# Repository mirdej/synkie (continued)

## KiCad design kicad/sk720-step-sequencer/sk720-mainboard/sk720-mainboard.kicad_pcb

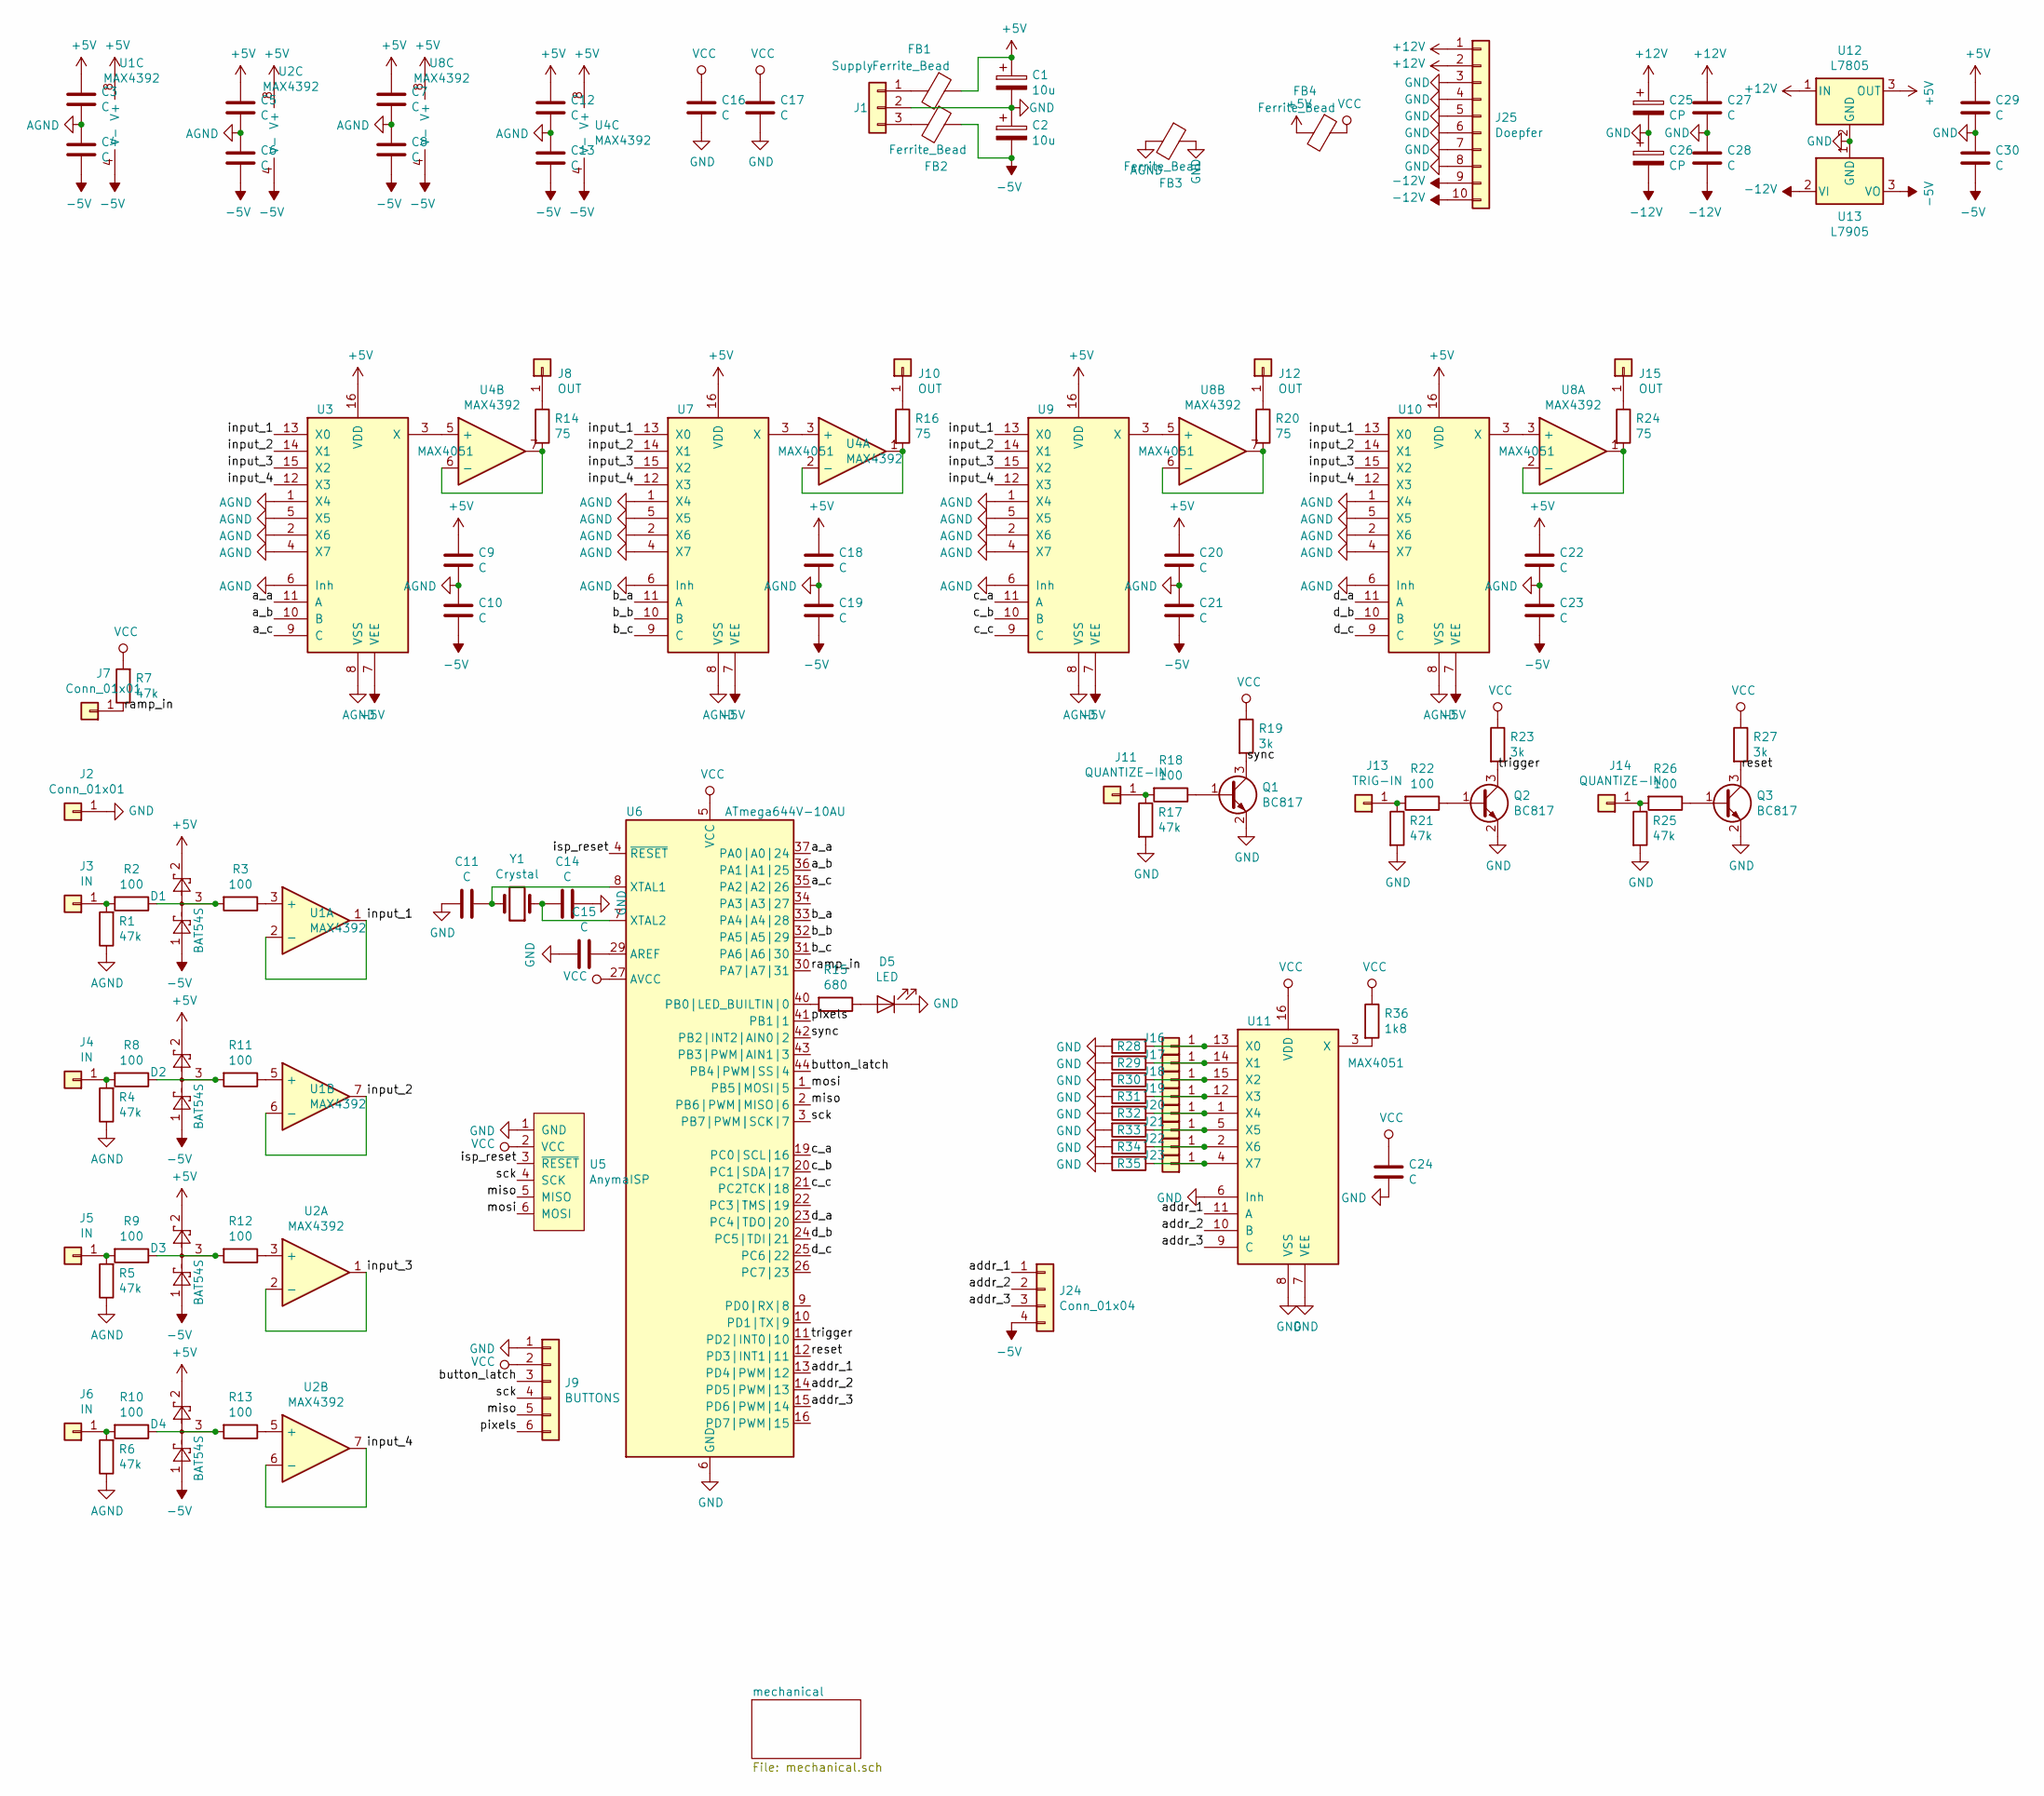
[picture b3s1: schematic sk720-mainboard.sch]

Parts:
C1, C2: 10u; CP_EIA-3528-21_Kemet-B
C3, C4, C5, C6, C7, C8, C9, C10, C11, C12, C13, C14, C15, C16, C17, C18, C19, C20, C21, C22, C23, C24, C27, C28, C29, C30: C; C_0603_1608Metric_Pad1.05x0.95mm_HandSolder
C25, C26: CP; CP_EIA-3528-21_Kemet-B_Pad1.50x2.35mm_HandSolder
D1, D2, D3, D4: BAT54S; SOT-23
D5: LED; LED_D3.0mm
FB1, FB2, FB3, FB4: Ferrite_Bead; L_1206_3216Metric_Pad1.42x1.75mm_HandSolder
J1: Supply; Molex_KK-254_AE-6410-03A_1x03_P2.54mm_Vertical
J2, J7: Conn_01x01; Solderpad_1mm
J3, J4, J5, J6: IN; Solderpad_1mm
J8, J10, J12, J15: OUT; Solderpad_1mm
J9: BUTTONS; PinHeader_1x06_P2.54mm_Vertical
J11, J14: QUANTIZE-IN; Solderpad_1mm
J13: TRIG-IN; Solderpad_1mm
J16, J17, J18, J19, J20, J21, J22, J23: TRIG; Solderpad_1mm
J24: Conn_01x04; PinHeader_1x04_P2.54mm_Vertical
J25: Doepfer; PinHeader_2x05_P2.54mm_Vertical
Q1, Q2, Q3: BC817; SOT-23
R1, R4, R5, R6, R7, R17, R21, R25: 47k; R_0805_2012Metric_Pad1.15x1.40mm_HandSolder
R2, R3, R8, R9, R10, R11, R12, R13, R18, R22, R26: 100; R_0805_2012Metric_Pad1.15x1.40mm_HandSolder
R14, R16, R20, R24: 75; R_0805_2012Metric_Pad1.15x1.40mm_HandSolder
R15: 680; R_0805_2012Metric_Pad1.15x1.40mm_HandSolder
R19, R23, R27: 3k; R_0805_2012Metric_Pad1.15x1.40mm_HandSolder
R28, R29, R30, R31, R32, R33, R34, R35: 300; R_0805_2012Metric_Pad1.15x1.40mm_HandSolder
R36: 1k8; R_0805_2012Metric_Pad1.15x1.40mm_HandSolder
U1, U2, U4, U8: MAX4392; SOIC-8_3.9x4.9mm_P1.27mm
U3, U7, U9, U10, U11: MAX4051; SOIC-16_3.9x9.9mm_P1.27mm
U5: AnymaISP; PinHeader_1x06_P2.54mm_Vertical
U6: ATmega644V-10AU; TQFP-44_10x10mm_P0.8mm
U12: L7805; TO-220-3_Horizontal_TabDown
U13: L7905; TO-220-3_Horizontal_TabDown
Y1: Crystal; Crystal_SMD_HC49-SD

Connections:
+5V: C1.1, C3.1, C5.1, C7.1, C9.1, C12.1, C18.1, C20.1, C22.1, C29.1, D1.2, D2.2, D3.2, D4.2, FB1.1, FB4.2, U1.8 (V+), U2.8 (V+), U3.16 (VDD), U4.8 (V+), U7.16 (VDD), U8.8 (V+), U9.16 (VDD), U10.16 (VDD), U12.3 (OUT)
+12V: C25.1, C27.1, J25.1, J25.2, U12.1 (IN)
-5V: C2.2, C4.2, C6.2, C8.2, C10.2, C13.2, C19.2, C21.2, C23.2, C30.2, D1.1, D2.1, D3.1, D4.1, FB2.1, J24.4, U1.4 (V-), U2.4 (V-), U3.7 (VEE), U4.4 (V-), U7.7 (VEE), U8.4 (V-), U9.7 (VEE), U10.7 (VEE), U13.3 (VO)
-12V: C26.2, C28.2, J25.9, J25.10, U13.2 (VI)
/a_a: U3.11 (A), U6.37 (PA0|A0|24)
/a_b: U3.10 (B), U6.36 (PA1|A1|25)
/a_c: U3.9 (C), U6.35 (PA2|A2|26)
/addr_1: J24.1, U6.13 (PD4|PWM|12), U11.11 (A)
/addr_2: J24.2, U6.14 (PD5|PWM|13), U11.10 (B)
/addr_3: J24.3, U6.15 (PD6|PWM|14), U11.9 (C)
/b_a: U6.33 (PA4|A4|28), U7.11 (A)
/b_b: U6.32 (PA5|A5|29), U7.10 (B)
/b_c: U6.31 (PA6|A6|30), U7.9 (C)
/button_latch: J9.3, U6.44 (PB4|PWM|SS|4)
/c_a: U6.19 (PC0|SCL|16), U9.11 (A)
/c_b: U6.20 (PC1|SDA|17), U9.10 (B)
/c_c: U6.21 (PC2TCK|18), U9.9 (C)
/d_a: U6.23 (PC4|TDO|20), U10.11 (A)
/d_b: U6.24 (PC5|TDI|21), U10.10 (B)
/d_c: U6.25 (PC6|22), U10.9 (C)
/input_1: U1.1, U1.2 (-), U3.13 (X0), U7.13 (X0), U9.13 (X0), U10.13 (X0)
/input_2: U1.6 (-), U1.7, U3.14 (X1), U7.14 (X1), U9.14 (X1), U10.14 (X1)
/input_3: U2.1, U2.2 (-), U3.15 (X2), U7.15 (X2), U9.15 (X2), U10.15 (X2)
/input_4: U2.6 (-), U2.7, U3.12 (X3), U7.12 (X3), U9.12 (X3), U10.12 (X3)
/isp_reset: U5.3 (~RESET), U6.4 (~RESET)
/miso: J9.5, U5.5 (MISO), U6.2 (PB6|PWM|MISO|6)
/mosi: U5.6 (MOSI), U6.1 (PB5|MOSI|5)
/pixels: J9.6, U6.41 (PB1|1)
/ramp_in: J7.1, R7.1, U6.30 (PA7|A7|31)
/reset: Q3.3 (C), R27.2, U6.12 (PD3|INT1|11)
/sck: J9.4, U5.4 (SCK), U6.3 (PB7|PWM|SCK|7)
/sync: Q1.3 (C), R19.2, U6.42 (PB2|INT2|AIN0|2)
/trigger: Q2.3 (C), R23.2, U6.11 (PD2|INT0|10)
AGND: C3.2, C4.1, C5.2, C6.1, C7.2, C8.1, C9.2, C10.1, C12.2, C13.1, C18.2, C19.1, C20.2, C21.1, C22.2, C23.1, FB3.2, R1.1, R4.1, R5.1, R6.1, U3.1 (X4), U3.2 (X6), U3.4 (X7), U3.5 (X5), U3.6 (Inh), U3.8 (VSS), U7.1 (X4), U7.2 (X6), U7.4 (X7), U7.5 (X5), U7.6 (Inh), U7.8 (VSS), U9.1 (X4), U9.2 (X6), U9.4 (X7), U9.5 (X5), U9.6 (Inh), U9.8 (VSS), U10.1 (X4), U10.2 (X6), U10.4 (X7), U10.5 (X5), U10.6 (Inh), U10.8 (VSS)
GND: C1.2, C2.1, C11.2, C14.1, C15.2, C16.2, C17.2, C24.2, C25.2, C26.1, C27.2, C28.1, C29.2, C30.1, D5.1 (K), FB3.1, J1.2, J2.1, J9.1, J25.3, J25.4, J25.5, J25.6, J25.7, J25.8, Q1.2 (E), Q2.2 (E), Q3.2 (E), R17.2, R21.2, R25.2, R28.2, R29.2, R30.2, R31.2, R32.2, R33.2, R34.2, R35.2, U5.1 (GND), U6.6 (GND), U6.18 (GND), U6.28 (GND), U6.39 (GND), U11.6 (Inh), U11.7 (VEE), U11.8 (VSS), U12.2 (GND), U13.1 (GND); also elsewhere on the board
unnamed: C11.1, U6.8 (XTAL1), Y1.2
unnamed: C14.2, U6.7 (XTAL2), Y1.1
unnamed: C15.1, U6.29 (AREF)
unnamed: D1.3, R2.1, R3.2
unnamed: D2.3, R8.1, R11.2
unnamed: D3.3, R9.1, R12.2
unnamed: D4.3, R10.1, R13.2
unnamed: D5.2 (A), R15.1
unnamed: FB1.2, J1.1
unnamed: FB2.2, J1.3
unnamed: J3.1, R1.2, R2.2
unnamed: J4.1, R4.2, R8.2
unnamed: J5.1, R5.2, R9.2
unnamed: J6.1, R6.2, R10.2
unnamed: J8.1, R14.1
unnamed: J10.1, R16.1
unnamed: J11.1, R17.1, R18.2
unnamed: J12.1, R20.1
unnamed: J13.1, R21.1, R22.2
unnamed: J14.1, R25.1, R26.2
unnamed: J15.1, R24.1
unnamed: J16.1, R28.1, U11.13 (X0)
unnamed: J17.1, R29.1, U11.14 (X1)
unnamed: J18.1, R30.1, U11.15 (X2)
unnamed: J19.1, R31.1, U11.12 (X3)
unnamed: J20.1, R32.1, U11.1 (X4)
unnamed: J21.1, R33.1, U11.5 (X5)
unnamed: J22.1, R34.1, U11.2 (X6)
unnamed: J23.1, R35.1, U11.4 (X7)
unnamed: Q1.1 (B), R18.1
unnamed: Q2.1 (B), R22.1
unnamed: Q3.1 (B), R26.1
unnamed: R3.1, U1.3 (+)
unnamed: R11.1, U1.5 (+)
unnamed: R12.1, U2.3 (+)
unnamed: R13.1, U2.5 (+)
unnamed: R14.2, U4.6 (-), U4.7
unnamed: R15.2, U6.40 (PB0|LED_BUILTIN|0)
unnamed: R16.2, U4.1, U4.2 (-)
unnamed: R20.2, U8.6 (-), U8.7
unnamed: R24.2, U8.1, U8.2 (-)
unnamed: R36.2, U11.3 (X)
unnamed: U3.3 (X), U4.5 (+)
unnamed: U4.3 (+), U7.3 (X)
unnamed: U8.5 (+), U9.3 (X)
unnamed: U8.3 (+), U10.3 (X)
VCC: C16.1, C17.1, C24.1, FB4.1, J9.2, R7.2, R19.1, R23.1, R27.1, R36.1, U5.2 (VCC), U6.5 (VCC), U6.17 (VCC), U6.27 (AVCC), U6.38 (VCC), U11.16 (VDD)

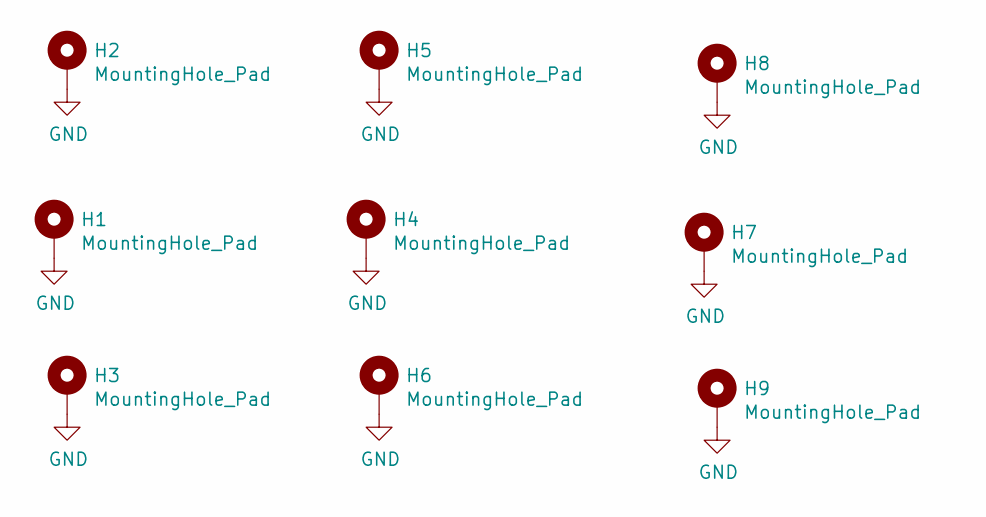
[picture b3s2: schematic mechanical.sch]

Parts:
H1, H2, H3, H4, H5, H6, H7, H8, H9: MountingHole_Pad; MountingHole_3.2mm_M3_ISO14580_Pad

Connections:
GND: H1.1, H2.1, H3.1, H4.1, H5.1, H6.1, H7.1, H8.1, H9.1; also elsewhere on the board

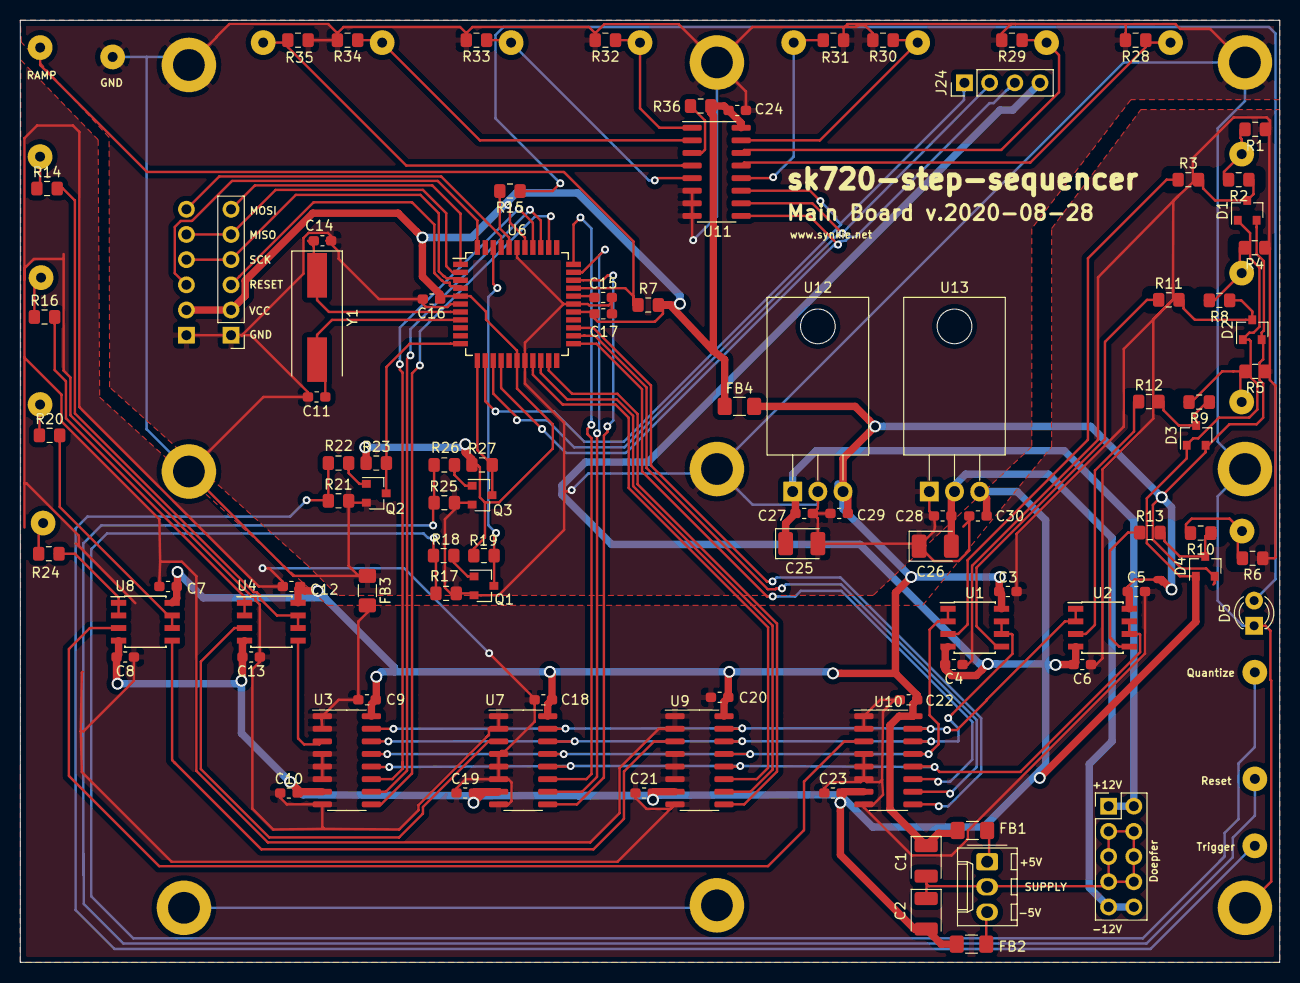
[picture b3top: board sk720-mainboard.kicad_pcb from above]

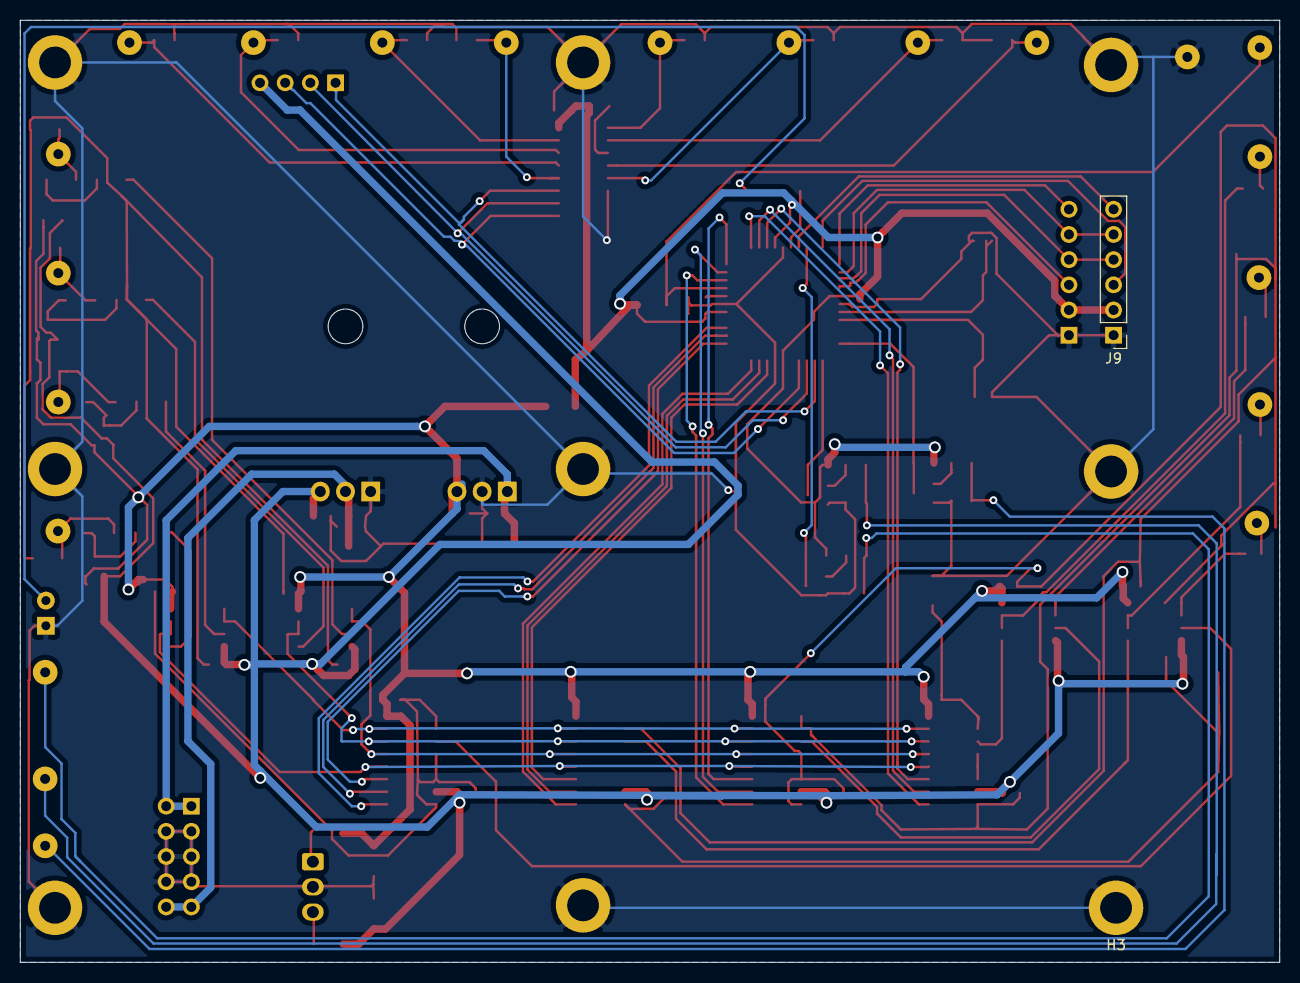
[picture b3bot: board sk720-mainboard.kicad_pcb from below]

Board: 2 copper layers, 127.0 x 95.0 mm, 126 parts (2 on the bottom side), 82 nets.

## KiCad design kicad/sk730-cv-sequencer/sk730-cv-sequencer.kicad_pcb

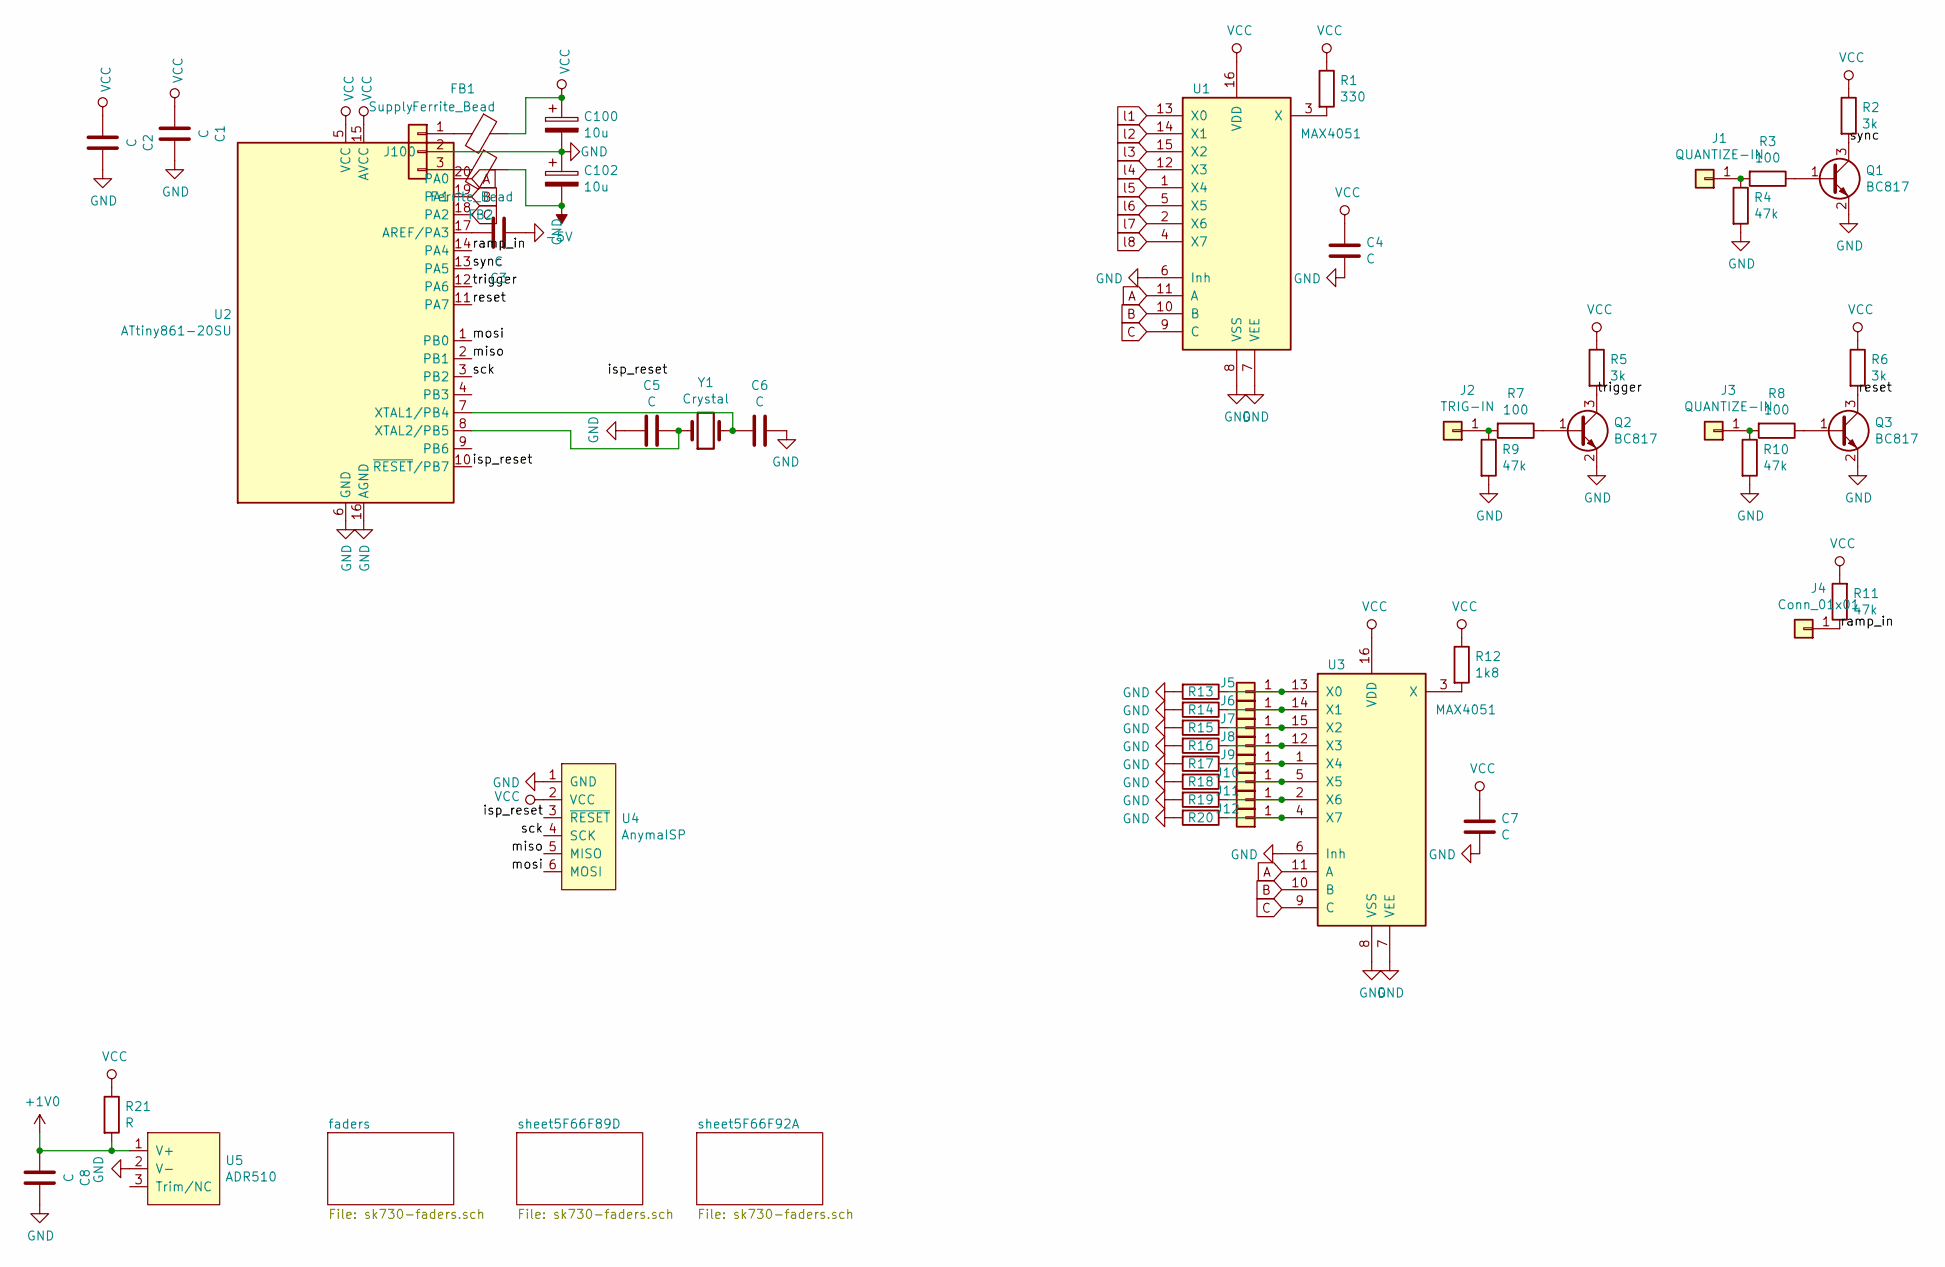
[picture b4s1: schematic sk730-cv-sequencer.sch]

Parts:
C1, C2, C3, C4, C7, C8: C; C_0603_1608Metric_Pad1.05x0.95mm_HandSolder
C5, C6: C; C_0805_2012Metric_Pad1.15x1.40mm_HandSolder
C100, C102: 10u; CP_EIA-3528-21_Kemet-B
FB1, FB2: Ferrite_Bead; L_1206_3216Metric_Pad1.42x1.75mm_HandSolder
J1, J3: QUANTIZE-IN; Solderpad_1mm
J2: TRIG-IN; Solderpad_1mm
J4: Conn_01x01; Solderpad_1mm
J5, J6, J7, J8, J9, J10, J11, J12: TRIG; Solderpad_1mm
J100: Supply; Molex_KK-254_AE-6410-03A_1x03_P2.54mm_Vertical
Q1, Q2, Q3: BC817; SOT-23
R1: 330; R_0805_2012Metric_Pad1.15x1.40mm_HandSolder
R2, R5, R6: 3k; R_0805_2012Metric_Pad1.15x1.40mm_HandSolder
R3, R7, R8: 100; R_0805_2012Metric_Pad1.15x1.40mm_HandSolder
R4, R9, R10, R11: 47k; R_0805_2012Metric_Pad1.15x1.40mm_HandSolder
R12: 1k8; R_0805_2012Metric_Pad1.15x1.40mm_HandSolder
R13, R14, R15, R16, R17, R18, R19, R20: 300; R_0805_2012Metric_Pad1.15x1.40mm_HandSolder
R21: R; C_0805_2012Metric_Pad1.15x1.40mm_HandSolder
U1, U3: MAX4051; SOIC-16_3.9x9.9mm_P1.27mm
U2: ATtiny861-20SU; SOIC-20W_7.5x12.8mm_P1.27mm
U4: AnymaISP; AnymaPOGO-ISP
U5: ADR510; SOT-23
Y1: Crystal; Crystal_SMD_HC49-SD

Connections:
+1V0: C8.2, R21.2, U5.1 (V+); also elsewhere on the board
-5V: C102.2, FB2.1; also elsewhere on the board
/isp_reset: U2.10 (~RESET~/PB7), U4.3 (~RESET)
/miso: U2.2 (PB1), U4.5 (MISO)
/mosi: U2.1 (PB0), U4.6 (MOSI)
/ramp_in: J4.1, R11.1, U2.14 (PA4)
/reset: Q3.3 (C), R6.2, U2.11 (PA7)
/sck: U2.3 (PB2), U4.4 (SCK)
/sync: Q1.3 (C), R2.2, U2.13 (PA5)
/trigger: Q2.3 (C), R5.2, U2.12 (PA6)
A: U1.11 (A), U2.20 (PA0), U3.11 (A); also elsewhere on the board
B: U1.10 (B), U2.19 (PA1), U3.10 (B); also elsewhere on the board
C: U1.9 (C), U2.18 (PA2), U3.9 (C); also elsewhere on the board
GND: C1.1, C2.1, C3.2, C4.2, C5.1, C6.2, C7.2, C8.1, C100.2, C102.1, J100.2, Q1.2 (E), Q2.2 (E), Q3.2 (E), R4.2, R9.2, R10.2, R13.2, R14.2, R15.2, R16.2, R17.2, R18.2, R19.2, R20.2, U1.6 (Inh), U1.7 (VEE), U1.8 (VSS), U2.6 (GND), U2.16 (AGND), U3.6 (Inh), U3.7 (VEE), U3.8 (VSS), U4.1 (GND), U5.2 (V-); also elsewhere on the board
unnamed: C3.1, U2.17 (AREF/PA3)
unnamed: C5.2, U2.8 (XTAL2/PB5), Y1.1
unnamed: C6.1, U2.7 (XTAL1/PB4), Y1.2
unnamed: FB1.2, J100.1
unnamed: FB2.2, J100.3
unnamed: J1.1, R3.2, R4.1
unnamed: J2.1, R7.2, R9.1
unnamed: J3.1, R8.2, R10.1
unnamed: J5.1, R13.1, U3.13 (X0)
unnamed: J6.1, R14.1, U3.14 (X1)
unnamed: J7.1, R15.1, U3.15 (X2)
unnamed: J8.1, R16.1, U3.12 (X3)
unnamed: J9.1, R17.1, U3.1 (X4)
unnamed: J10.1, R18.1, U3.5 (X5)
unnamed: J11.1, R19.1, U3.2 (X6)
unnamed: J12.1, R20.1, U3.4 (X7)
unnamed: Q1.1 (B), R3.1
unnamed: Q2.1 (B), R7.1
unnamed: Q3.1 (B), R8.1
unnamed: R1.2, U1.3 (X)
unnamed: R12.2, U3.3 (X)
VCC: C1.2, C2.2, C4.1, C7.1, C100.1, FB1.1, R1.1, R2.1, R5.1, R6.1, R11.2, R12.1, R21.1, U1.16 (VDD), U2.5 (VCC), U2.15 (AVCC), U3.16 (VDD), U4.2 (VCC); also elsewhere on the board
l1: U1.13 (X0); also elsewhere on the board
l2: U1.14 (X1); also elsewhere on the board
l3: U1.15 (X2); also elsewhere on the board
l4: U1.12 (X3); also elsewhere on the board
l5: U1.1 (X4); also elsewhere on the board
l6: U1.5 (X5); also elsewhere on the board
l7: U1.2 (X6); also elsewhere on the board
l8: U1.4 (X7); also elsewhere on the board

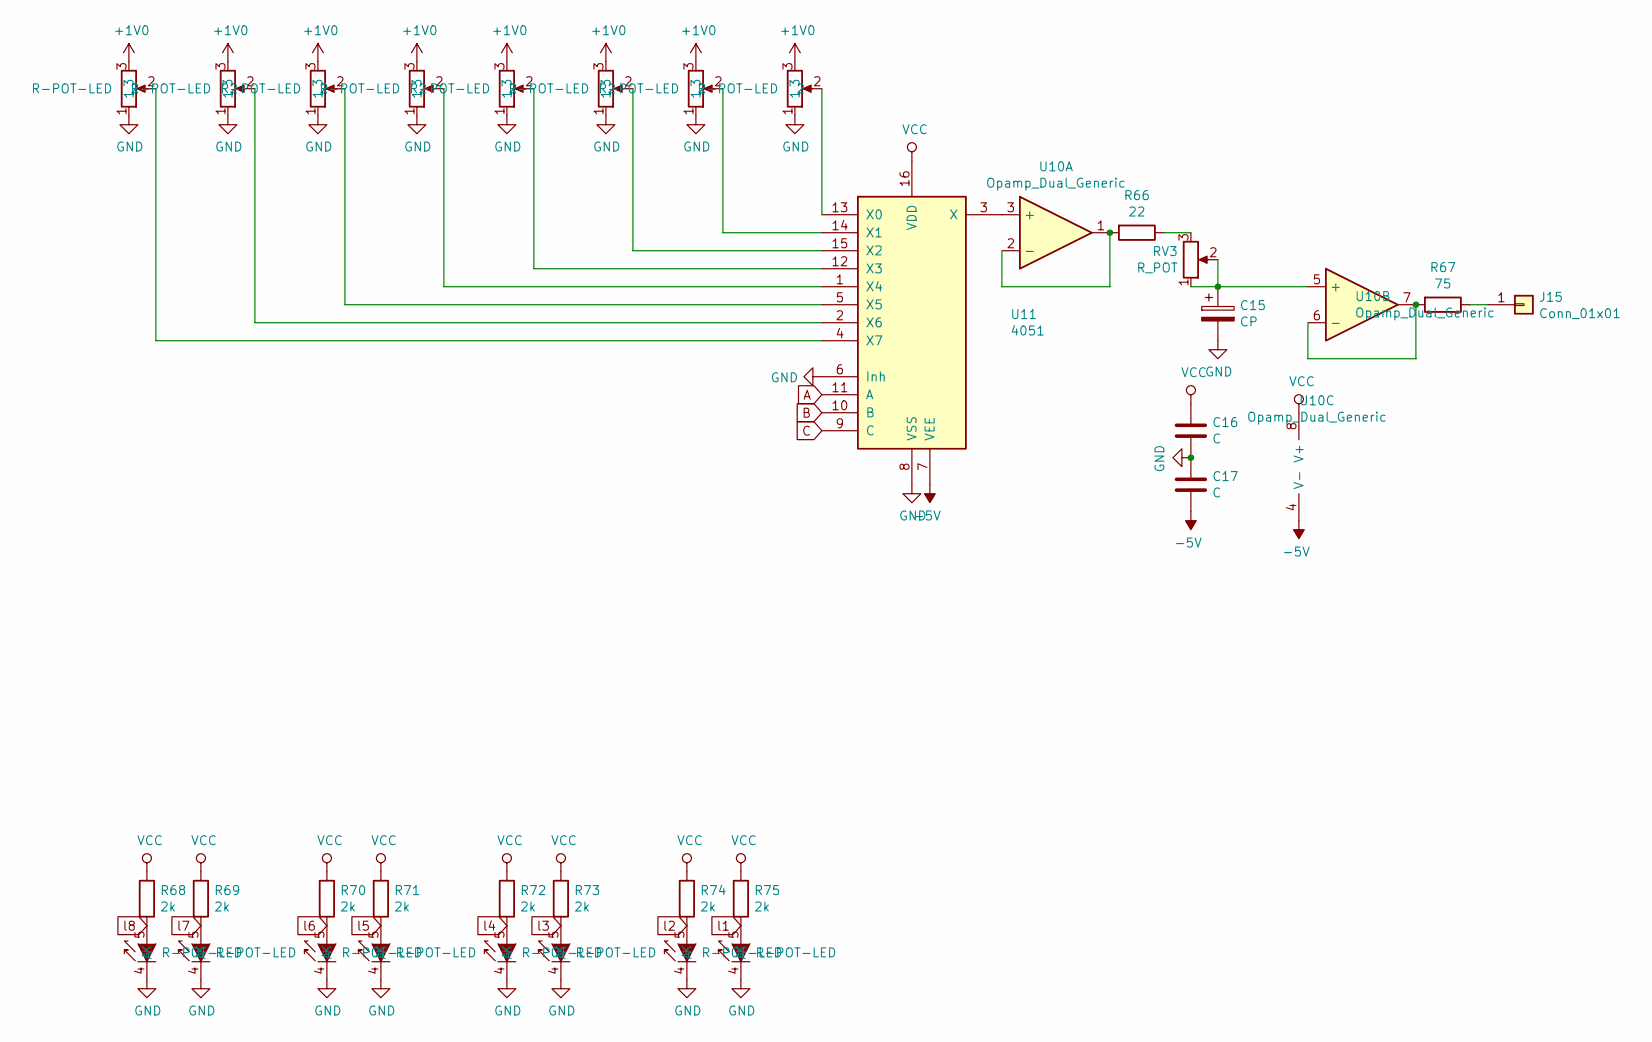
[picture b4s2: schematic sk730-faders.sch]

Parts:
C9: CP; CP_EIA-3528-21_Kemet-B_Pad1.50x2.35mm_HandSolder
C10, C11: C; C_0603_1608Metric_Pad1.05x0.95mm_HandSolder
J13: Conn_01x01; Solderpad_1mm
R22, R23, R24, R25, R26, R27, R28, R29: R-POT-LED; PTL20
R30: 22; C_0805_2012Metric_Pad1.15x1.40mm_HandSolder
R31: 75; C_0805_2012Metric_Pad1.15x1.40mm_HandSolder
R32, R33, R34, R35, R36, R37, R38, R39: 2k; R_0805_2012Metric_Pad1.15x1.40mm_HandSolder
RV1: R_POT; Potentiometer_Alps_RK09K_Single_Vertical
U6: Opamp_Dual_Generic; SOIC-8_3.9x4.9mm_P1.27mm
U7: 4051; SOIC-16_3.9x9.9mm_P1.27mm

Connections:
+1V0: R22.3, R23.3, R24.3, R25.3, R26.3, R27.3, R28.3, R29.3; also elsewhere on the board
-5V: C11.2, U6.4 (V-), U7.7 (VEE); also elsewhere on the board
A: U7.11 (A); also elsewhere on the board
B: U7.10 (B); also elsewhere on the board
C: U7.9 (C); also elsewhere on the board
GND: C9.2, C10.2, C11.1, R22.1, R22.4 (K), R23.1, R23.4 (K), R24.1, R24.4 (K), R25.1, R25.4 (K), R26.1, R26.4 (K), R27.1, R27.4 (K), R28.1, R28.4 (K), R29.1, R29.4 (K), U7.6 (Inh), U7.8 (VSS); also elsewhere on the board
unnamed: C9.1, RV1.1, RV1.2, U6.5 (+)
unnamed: J13.1, R31.1
unnamed: R22.2, U7.4 (X7)
unnamed: R23.2, U7.2 (X6)
unnamed: R24.2, U7.5 (X5)
unnamed: R25.2, U7.1 (X4)
unnamed: R26.2, U7.12 (X3)
unnamed: R27.2, U7.15 (X2)
unnamed: R28.2, U7.14 (X1)
unnamed: R29.2, U7.13 (X0)
unnamed: R30.1, RV1.3
unnamed: R30.2, U6.1, U6.2 (-)
unnamed: R31.2, U6.6 (-), U6.7
unnamed: U6.3 (+), U7.3 (X)
VCC: C10.1, R32.1, R33.1, R34.1, R35.1, R36.1, R37.1, R38.1, R39.1, U6.8 (V+), U7.16 (VDD); also elsewhere on the board
l1: R29.5 (A), R39.2; also elsewhere on the board
l2: R28.5 (A), R38.2; also elsewhere on the board
l3: R27.5 (A), R37.2; also elsewhere on the board
l4: R26.5 (A), R36.2; also elsewhere on the board
l5: R25.5 (A), R35.2; also elsewhere on the board
l6: R24.5 (A), R34.2; also elsewhere on the board
l7: R23.5 (A), R33.2; also elsewhere on the board
l8: R22.5 (A), R32.2; also elsewhere on the board

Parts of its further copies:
C12, C15: CP; CP_EIA-3528-21_Kemet-B_Pad1.50x2.35mm_HandSolder
C13, C14, C16, C17: C; C_0603_1608Metric_Pad1.05x0.95mm_HandSolder
J14, J15: Conn_01x01; Solderpad_1mm
R40, R41, R42, R43, R44, R45, R46, R47, R58, R59, R60, R61, R62, R63, R64, R65: R-POT-LED; PTL20
R48, R66: 22; C_0805_2012Metric_Pad1.15x1.40mm_HandSolder
R49, R67: 75; C_0805_2012Metric_Pad1.15x1.40mm_HandSolder
R50, R51, R52, R53, R54, R55, R56, R57, R68, R69, R70, R71, R72, R73, R74, R75: 2k; R_0805_2012Metric_Pad1.15x1.40mm_HandSolder
RV2, RV3: R_POT; Potentiometer_Alps_RK09K_Single_Vertical
U8, U10: Opamp_Dual_Generic; SOIC-8_3.9x4.9mm_P1.27mm
U9, U11: 4051; SOIC-16_3.9x9.9mm_P1.27mm

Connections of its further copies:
+1V0: R40.3, R41.3, R42.3, R43.3, R44.3, R45.3, R46.3, R47.3, R58.3, R59.3, R60.3, R61.3, R62.3, R63.3, R64.3, R65.3; also elsewhere on the board
-5V: C14.2, C17.2, U8.4 (V-), U9.7 (VEE), U10.4 (V-), U11.7 (VEE); also elsewhere on the board
A: U9.11 (A), U11.11 (A); also elsewhere on the board
B: U9.10 (B), U11.10 (B); also elsewhere on the board
C: U9.9 (C), U11.9 (C); also elsewhere on the board
GND: C12.2, C13.2, C14.1, C15.2, C16.2, C17.1, R40.1, R40.4 (K), R41.1, R41.4 (K), R42.1, R42.4 (K), R43.1, R43.4 (K), R44.1, R44.4 (K), R45.1, R45.4 (K), R46.1, R46.4 (K), R47.1, R47.4 (K), R58.1, R58.4 (K), R59.1, R59.4 (K), R60.1, R60.4 (K), R61.1, R61.4 (K), R62.1, R62.4 (K), R63.1, R63.4 (K), R64.1, R64.4 (K), R65.1, R65.4 (K), U9.6 (Inh), U9.8 (VSS), U11.6 (Inh), U11.8 (VSS); also elsewhere on the board
unnamed: C12.1, RV2.1, RV2.2, U8.5 (+)
unnamed: C15.1, RV3.1, RV3.2, U10.5 (+)
unnamed: J14.1, R49.1
unnamed: J15.1, R67.1
unnamed: R40.2, U9.4 (X7)
unnamed: R41.2, U9.2 (X6)
unnamed: R42.2, U9.5 (X5)
unnamed: R43.2, U9.1 (X4)
unnamed: R44.2, U9.12 (X3)
unnamed: R45.2, U9.15 (X2)
unnamed: R46.2, U9.14 (X1)
unnamed: R47.2, U9.13 (X0)
unnamed: R48.1, RV2.3
unnamed: R48.2, U8.1, U8.2 (-)
unnamed: R49.2, U8.6 (-), U8.7
unnamed: R58.2, U11.4 (X7)
unnamed: R59.2, U11.2 (X6)
unnamed: R60.2, U11.5 (X5)
unnamed: R61.2, U11.1 (X4)
unnamed: R62.2, U11.12 (X3)
unnamed: R63.2, U11.15 (X2)
unnamed: R64.2, U11.14 (X1)
unnamed: R65.2, U11.13 (X0)
unnamed: R66.1, RV3.3
unnamed: R66.2, U10.1, U10.2 (-)
unnamed: R67.2, U10.6 (-), U10.7
unnamed: U8.3 (+), U9.3 (X)
unnamed: U10.3 (+), U11.3 (X)
VCC: C13.1, C16.1, R50.1, R51.1, R52.1, R53.1, R54.1, R55.1, R56.1, R57.1, R68.1, R69.1, R70.1, R71.1, R72.1, R73.1, R74.1, R75.1, U8.8 (V+), U9.16 (VDD), U10.8 (V+), U11.16 (VDD); also elsewhere on the board
l1: R47.5 (A), R57.2, R65.5 (A), R75.2; also elsewhere on the board
l2: R46.5 (A), R56.2, R64.5 (A), R74.2; also elsewhere on the board
l3: R45.5 (A), R55.2, R63.5 (A), R73.2; also elsewhere on the board
l4: R44.5 (A), R54.2, R62.5 (A), R72.2; also elsewhere on the board
l5: R43.5 (A), R53.2, R61.5 (A), R71.2; also elsewhere on the board
l6: R42.5 (A), R52.2, R60.5 (A), R70.2; also elsewhere on the board
l7: R41.5 (A), R51.2, R59.5 (A), R69.2; also elsewhere on the board
l8: R40.5 (A), R50.2, R58.5 (A), R68.2; also elsewhere on the board
